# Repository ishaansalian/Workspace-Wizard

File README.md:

# Workspace Wizard

**Team Members:**  
- Ishaan Salian  
- Aryaman Ghura 
- Kavya Manchanda  
- Mary Esenther

**Project Overview**  
Workspace Wizard is an autonomous desk organization system designed to optimize workspace management by identifying, sorting, and organizing objects on a desk. The system uses a combination of hardware and software to detect object positions, plan efficient placement paths, and execute movements to organize objects with high precision.

**Key Features:**  
- **Object Detection & Recognition:** The system uses a camera and machine learning models to identify and track objects on the desk.
- **Pathfinding Algorithm:** The robot calculates optimal paths for organizing objects, avoiding obstacles and ensuring an efficient layout.
- **Autonomous Movement:** The robot uses motors and tracks to move objects into predefined positions while respecting boundaries and object types.
- **Task Automation:** The robot performs "knolling" (arranging objects neatly and systematically) by aligning objects with a target orientation and spacing.

**Technologies Used:**  
- **Hardware:**  
  - Nvidia Jetson (for processing and computation)  
  - Servo motors and tracks (for movement)
  - Custom PCB (for controls)
  - USB Camera (for object detection and tracking)  
  - Power management system (for optimal battery usage)  
- **Software:**  
  - Python (for control logic and algorithms)  
  - OpenCV (for computer vision tasks)

**References:**  
- Hu, Y., Zhang, Z., Zhu, X., Liu, R., Philippe Martin Wyder, & Lipson, H. (2023). Knolling bot: Learning robotic object arrangement from tidy demonstrations. https://api.semanticscholar.org/CorpusID:268513198

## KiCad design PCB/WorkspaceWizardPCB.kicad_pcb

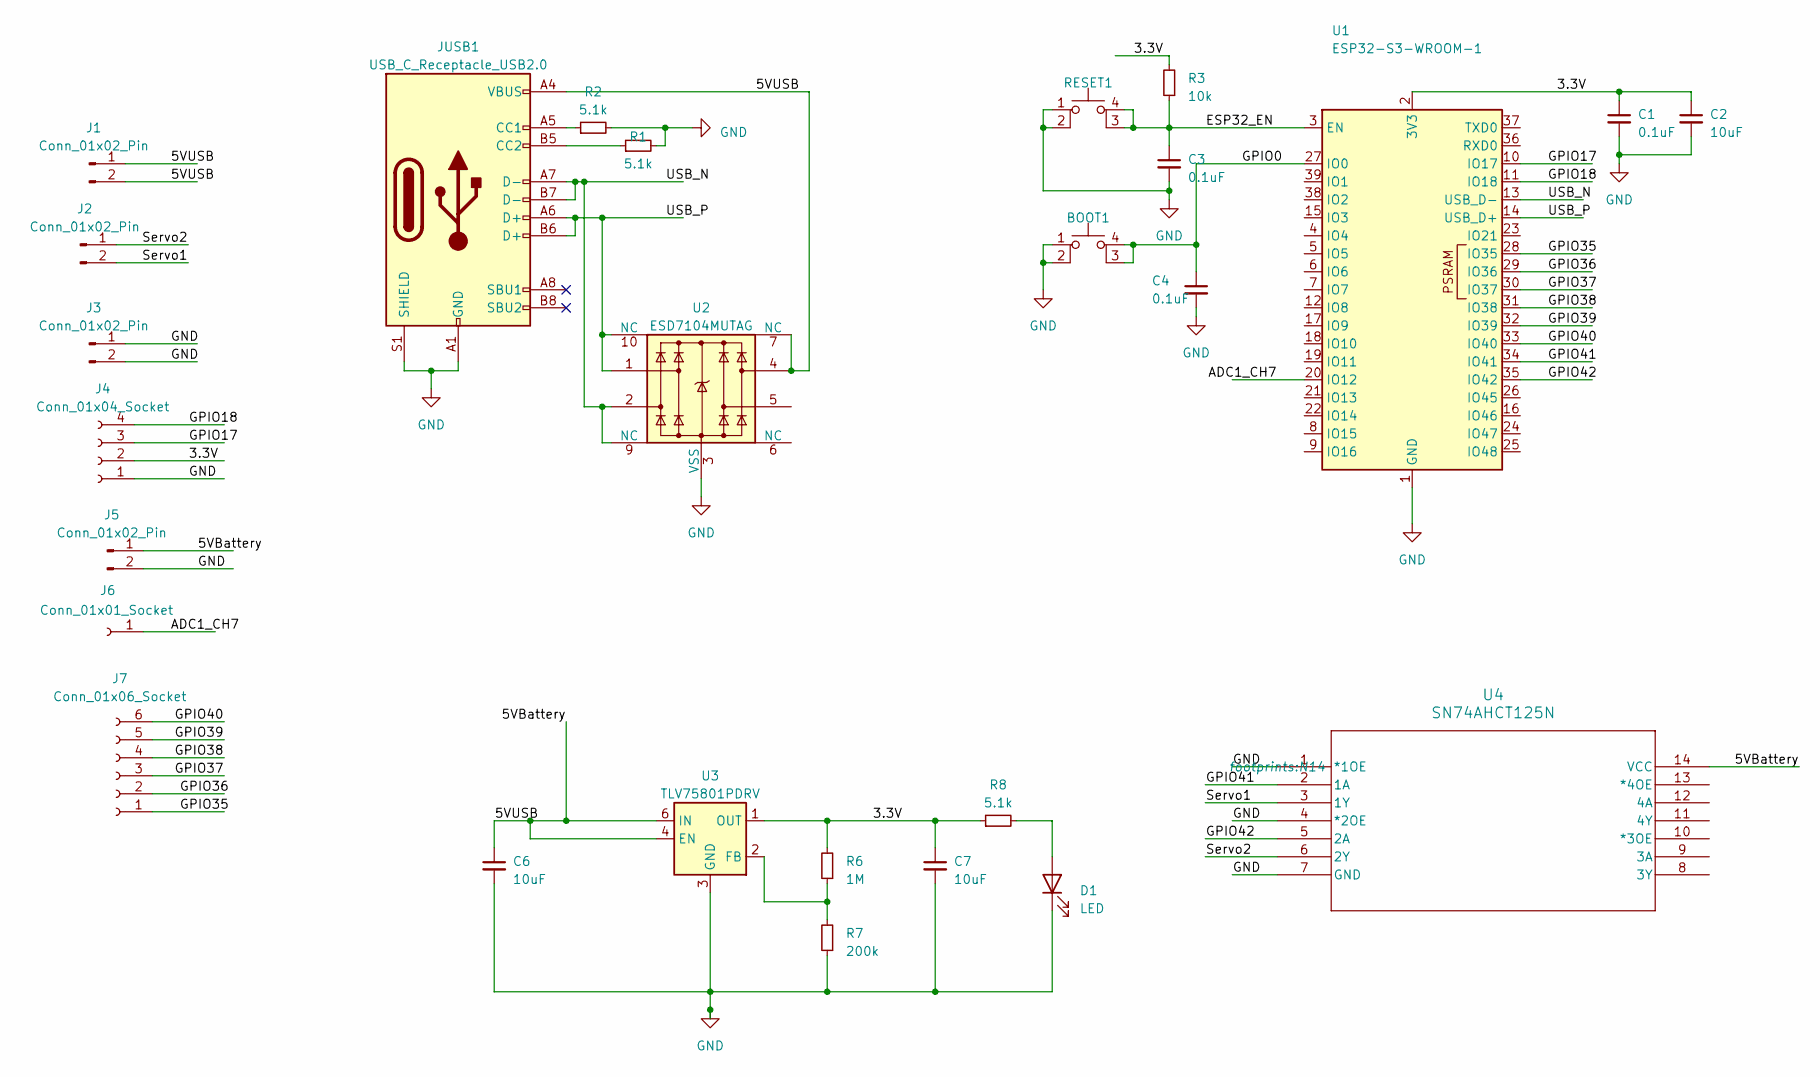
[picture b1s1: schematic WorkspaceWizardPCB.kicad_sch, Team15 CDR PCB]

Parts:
BOOT1: SW_SPST_PTS810
C1, C3, C4: 0.1uF; C_0603_1608Metric; LCSC C701321
C2, C6, C7: 10uF; C_0603_1608Metric; LCSC C38898
D1: LED; LED_0603_1608Metric; LCSC C9900030205
J1, J2, J3, J5: Conn_01x02_Pin; PinHeader_1x02_P2.54mm_Vertical
J4: Conn_01x04_Socket; PinSocket_1x04_P2.54mm_Vertical
J6: Conn_01x01_Socket; PinSocket_1x01_P2.54mm_Vertical
J7: Conn_01x06_Socket; PinSocket_1x06_P2.54mm_Vertical
JUSB1: USB_C_Receptacle_USB2.0; USB_C_Receptacle_GCT_USB4105-xx-A_16P_TopMnt_Horizontal; LCSC C3020560
R1, R2, R8: 5.1k; R_0603_1608Metric; LCSC C881139
R3: 10k; R_0603_1608Metric; LCSC C881132
R6: 1M; R_0603_1608Metric; LCSC C22935
R7: 200k; R_0603_1608Metric; LCSC C881135
RESET1: SW_SPST_PTS810
U1: ESP32-S3-WROOM-1; LCSC C2913201
U2: ESD7104MUTAG; Diodes_UDFN-10_1.0x2.5mm_P0.5mm; LCSC C1980462
U3: TLV75801PDRV; WSON-6-1EP_2x2mm_P0.65mm_EP1x1.6mm; LCSC C2876308
U4: SN74AHCT125N; N14

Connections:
/3.3V: C1.1, C2.1, C7.1, J4.2, R3.2, R6.2, R8.1, U1.2 (3V3), U3.1 (OUT)
/5VBattery: C6.1, J1.1, J1.2, J5.1, JUSB1.A4 (VBUS), JUSB1.A9 (VBUS), JUSB1.B4 (VBUS), JUSB1.B9 (VBUS), U2.4, U2.7 (NC), U3.4 (EN), U3.6 (IN), U4.14 (VCC)
/ADC1_CH7: J6.1, U1.20 (IO12)
/ESP32_EN: C3.1, R3.1, RESET1.3 (K), RESET1.4 (A), U1.3 (EN)
/GPIO0: BOOT1.3 (K), BOOT1.4 (A), C4.1, U1.27 (IO0)
/GPIO17: J4.3, U1.10 (IO17)
/GPIO18: J4.4, U1.11 (IO18)
/GPIO35: J7.1, U1.28 (IO35)
/GPIO36: J7.2, U1.29 (IO36)
/GPIO37: J7.3, U1.30 (IO37)
/GPIO38: J7.4, U1.31 (IO38)
/GPIO39: J7.5, U1.32 (IO39)
/GPIO40: J7.6, U1.33 (IO40)
/GPIO41: U1.34 (IO41), U4.2 (1A)
/GPIO42: U1.35 (IO42), U4.5 (2A)
/Servo1: J2.2, U4.3 (1Y)
/Servo2: J2.1, U4.6 (2Y)
/USB_N: JUSB1.A7 (D-), JUSB1.B7 (D-), U1.13 (USB_D-), U2.2, U2.9 (NC)
/USB_P: JUSB1.A6 (D+), JUSB1.B6 (D+), U1.14 (USB_D+), U2.1, U2.10 (NC)
GND: BOOT1.1, BOOT1.2, C1.2, C2.2, C3.2, C4.2, C6.2, C7.2, D1.1 (K), J3.1, J3.2, J4.1, J5.2, JUSB1.A1 (GND), JUSB1.A12 (GND), JUSB1.B1 (GND), JUSB1.B12 (GND), JUSB1.S1 (SHIELD), R1.2, R2.2, R7.1, RESET1.1, RESET1.2, U1.1 (GND), U1.40 (GND), U1.41 (GND), U2.3 (VSS), U2.8 (VSS), U3.3 (GND), U3.7 (GND), U4.1 (*1OE), U4.4 (*2OE), U4.7 (GND)
unnamed: D1.2 (A), R8.2
unnamed: JUSB1.A5 (CC1), R2.1
unnamed: JUSB1.B5 (CC2), R1.1
unnamed: R6.1, R7.2, U3.2 (FB)

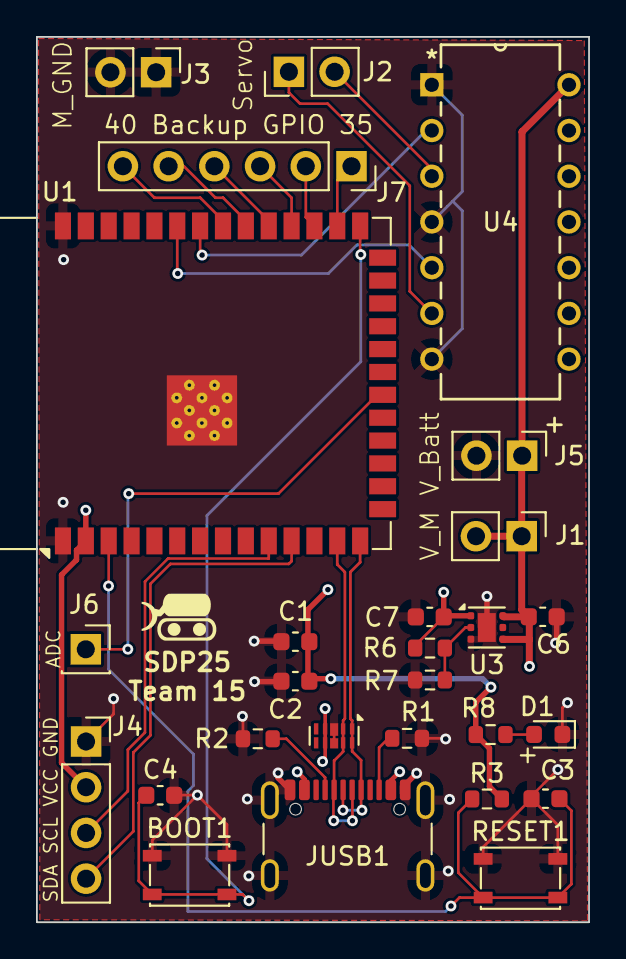
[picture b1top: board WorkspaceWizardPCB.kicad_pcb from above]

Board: 4 copper layers, 30.7 x 49.2 mm, 27 parts (0 on the bottom side), 24 nets.

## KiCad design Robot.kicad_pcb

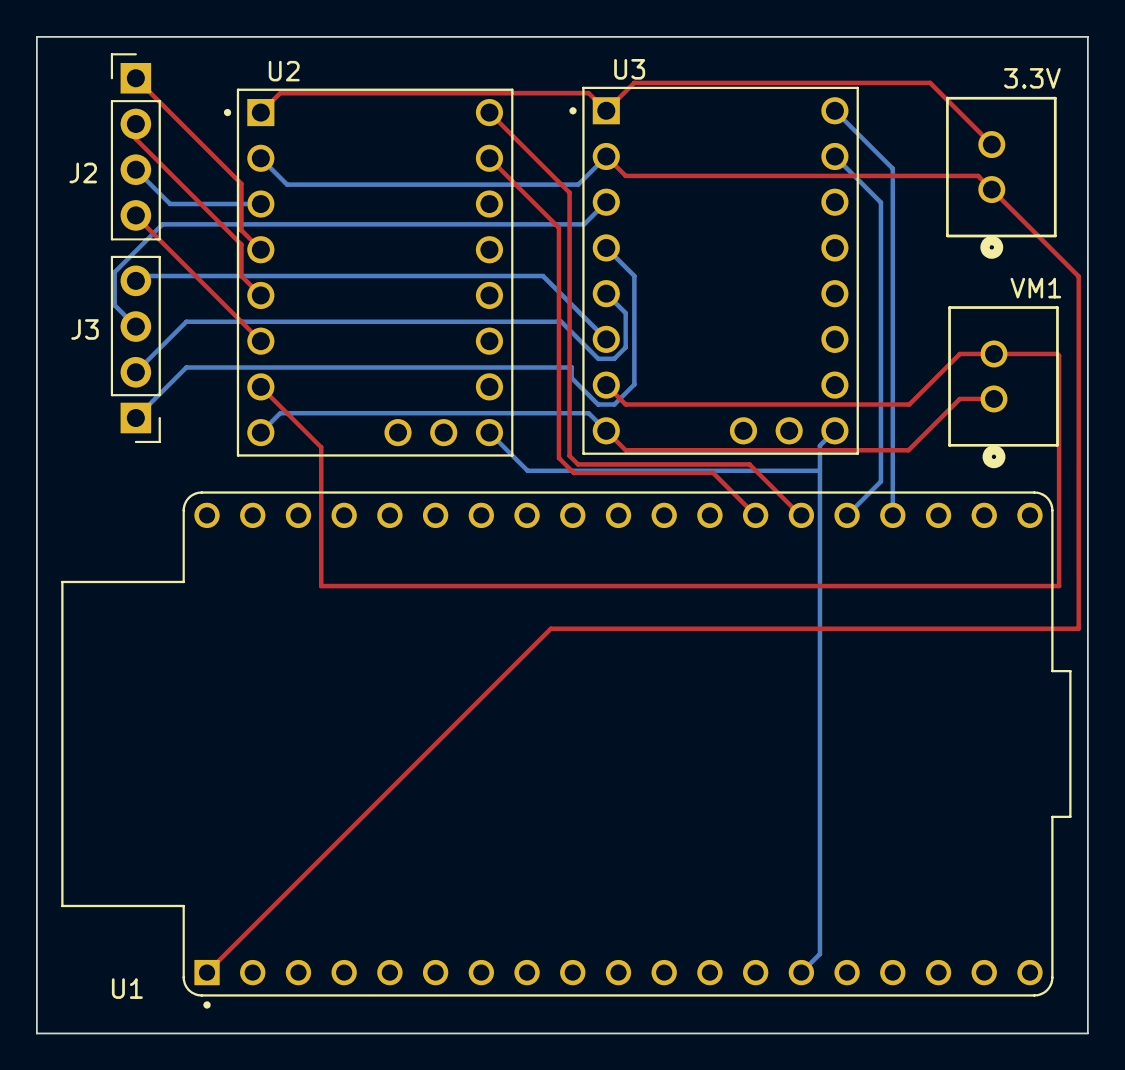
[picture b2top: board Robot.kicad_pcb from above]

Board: 2 copper layers, 58.4 x 55.4 mm, 7 parts (0 on the bottom side), 15 nets.

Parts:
3.3V: B2B-XH-A; CONN_B2B-XH-A_JST
J2, J3: Conn_01x04; PinHeader_1x04_P2.54mm_Vertical
U1: ESP32-DEVKITC-32E; MODULE_ESP32-DEVKITC-32E
U2, U3: TMC2209_SILENTSTEPSTICK; MODULE_TMC2209_SILENTSTEPSTICK
VM1: B2B-XH-A; CONN_B2B-XH-A_JST

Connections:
GND: 3.3V.2, U1.J2_14 (GND_J2_14), U2.1 (GND), U2.7 (GND), U2.16 (~EN), U3.1 (GND), U3.7 (GND), U3.16 (~EN), VM1.2
unnamed: J2.1, U2.4 (M1A)
unnamed: J2.2, U2.5 (M2A)
unnamed: J2.3, U2.3 (M1B)
unnamed: J2.4, U2.6 (M2B)
unnamed: J3.1, U3.4 (M1A)
unnamed: J3.2, U3.5 (M2A)
unnamed: J3.3, U3.3 (M1B)
unnamed: J3.4, U3.6 (M2B)
unnamed: U1.J3_14 (IO0), U2.9 (DIR)
unnamed: U1.J3_15 (IO2), U3.10 (STEP)
unnamed: U1.J3_13 (IO4), U2.10 (STEP)
unnamed: U1.J3_16 (IO15), U3.9 (DIR)
VCC 22V: U2.8 (VM), U3.8 (VM), VM1.1
VIO 3.3V: 3.3V.1, U1.J2_1 (3V3), U2.2 (VIO), U3.2 (VIO)

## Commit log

2024-11-24 folder
2024-11-24 Create PCB
2024-11-24 added PCB
2024-11-26 Segment.py
2024-12-23 Rename ESP32TMC2209test.ino to Movement.ino
2025-02-15 Added Aruco detection alg
2025-02-28 Created using Colab
2025-03-06 delete
2025-03-06 added KiCad files
2025-03-10 Bot tracking
    Tracks two fiducials to crop and flatten output image, and detects robot within that image by its corners. The corners are printed out, and the cropped image is saved to the file system. Don't leave 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
2025-03-11 uses fiducials to give robot commands
2025-03-12 Updated to auto-detect the ESP32 by its name
2025-03-13 updated to auto-detect the ESP32 by its name and find address
2025-03-13 updated to print battery along with voltage
2025-03-25 Create aruco_markers folder
2025-03-31 Calibration checkerboard
    Dimensions are 12x8, which is listed as 11x7 in the code. If this is ever changed, we'll need to match the size with a new chessboard.
2025-04-01 Rename #15 CDR Slides.pdf to Slides/#15 CDR Slides.pdf
2025-04-01 Rename #15 MDR Slides.pdf to Slides/#15 MDR Slides.pdf
2025-04-01 Rename #15 PDR Slides.pdf to Slides/#15 PDR Slides.pdf
2025-04-12 Add files via upload
    april12 (aruco test)
2025-04-12 Add files via upload
    april12 initialization test
2025-04-15 Robot movement w/ course correction
2025-05-17 Added Final Report
